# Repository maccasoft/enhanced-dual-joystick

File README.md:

## Enhanced Dual Joystick for RC2014

Add-on board designed for the [RC2014](http://rc2014.co.uk/) computer to provide an enhanced dual joystick port for games and other applications.

The board is based on a Z80 PIO that provide two 8-bit bi-direction parallel ports. Software can configure each port independently to use a standard Atari-compatibile joystick, a NES-compatible gamepad or any
other controller driven by digital I/O lines.

I/O ports can be configured with the on-board dip-switch.

### Schematics

| Parts List  |                                     |
| ----------- | ----------------------------------- |
| R1          | 10.000 ohm 1/4 watt                 |
| RN1, RN2    | 10.000 ohm, 9-pin resistor network  |
| RN3         | 10.000 ohm, 7-pin resistor network  |
| C1, C2      | 100.000 pF polyester                |
| IC1         | Z84C2010PEG                         |
| IC2         | CD74HCT688N                         |
| S1          | DIP-switch                          |
| CN1         | 40 pin male header, right angle     |
| CN2, CN3    | DB9 male connector                  |

Additionally, a NES-compatible gamepad board is included for those who don't have access to an existing joystick.

| Parts List            |                           |
| --------------------- | ------------------------- |
| R1-R8                 | 10.000 ohm 1/4 watt       |
| C1                    | 100.000 pF polyester      |
| IC1                   | CD4021                    |
| UP, DOWN, LEFT, RIGHT | 6x6 mm tact switches      |
| SELECT, START, B, A   | 6x6 mm tact switches      |
| CN1                   | 5-pin connector           |

### Code Examples

The Z80 PIO must be initialized at startup by configuring both ports in control mode 3 followed by the pin direction settings appropriate for
the game controller type.

**Atari 2600 joystick.**

```
PIO_BASE    .EQU    70H

            ; initialize

            LD      A,0CFH              ; set port A mode 3 (control)
            OUT     (PIO_BASE+1),A
            LD      A,0FFH              ; all pins as input
            OUT     (PIO_BASE+1),A

            LD      A,0CFH              ; set port B mode 3 (control)
            OUT     (PIO_BASE+3),A
            LD      A,0FFH              ; all pins as input
            OUT     (PIO_BASE+3),A

            ; read joystick 1

            IN      A,(PIO_BASE)

            ; read joystick 2

            IN      A,(PIO_BASE+2)
```

**NES gamepad on Joystick 2.**

The code assumes that the gamepad is wired to the DB9 connector as follows: 4=data, 5=load, 6=clk.  

```
PIO_BASE    .EQU    70H

NES_LOAD    .EQU    20H
NES_CLK     .EQU    10H

            ; initialize

            LD      A,0CFH              ; set port A mode 3 (control)
            OUT     (PIO_BASE+1),A
            LD      A,0FFH              ; all pins as input
            OUT     (PIO_BASE+1),A

            LD      A,0CFH              ; set port B mode 3 (control)
            OUT     (PIO_BASE+3),A
            LD      A,~(NES_LOAD|NES_CLK)   ; clock and load pins as output, others as input
            OUT     (PIO_BASE+3),A
            LD      A,0
            OUT     (PIO_BASE+2),A

            ; read joystick 1

            IN      A,(PIO_BASE)

            ; read joystick 2

            LD      C,0

            LD      A,NES_LOAD          ; pulse load pin
            OUT     ((PIO_BASE+2),A
            LD      A,0
            OUT     (PIO_BASE+2),A

            LD      B,8
L1:         IN      A,(PIO_BASE+2)      ; read data from bit 0
            RRA
            RL      C

            LD      A,NES_CLOCK         ; pulse clock
            OUT     (PIO_BASE+2),A
            LD      A,0
            OUT     (PIO_BASE+2),A

            DJNZ    L1

            LD      A,C
```

### Boards

Boards are shared on OSHPark:

[Dual Joystick](https://oshpark.com/shared_projects/1jlMB1r2)  
[Game Controller](https://oshpark.com/shared_projects/LxgxoR9j)  

A [donation](https://www.paypal.me/maccasoft/5eur) to support this and future projects is always welcome!

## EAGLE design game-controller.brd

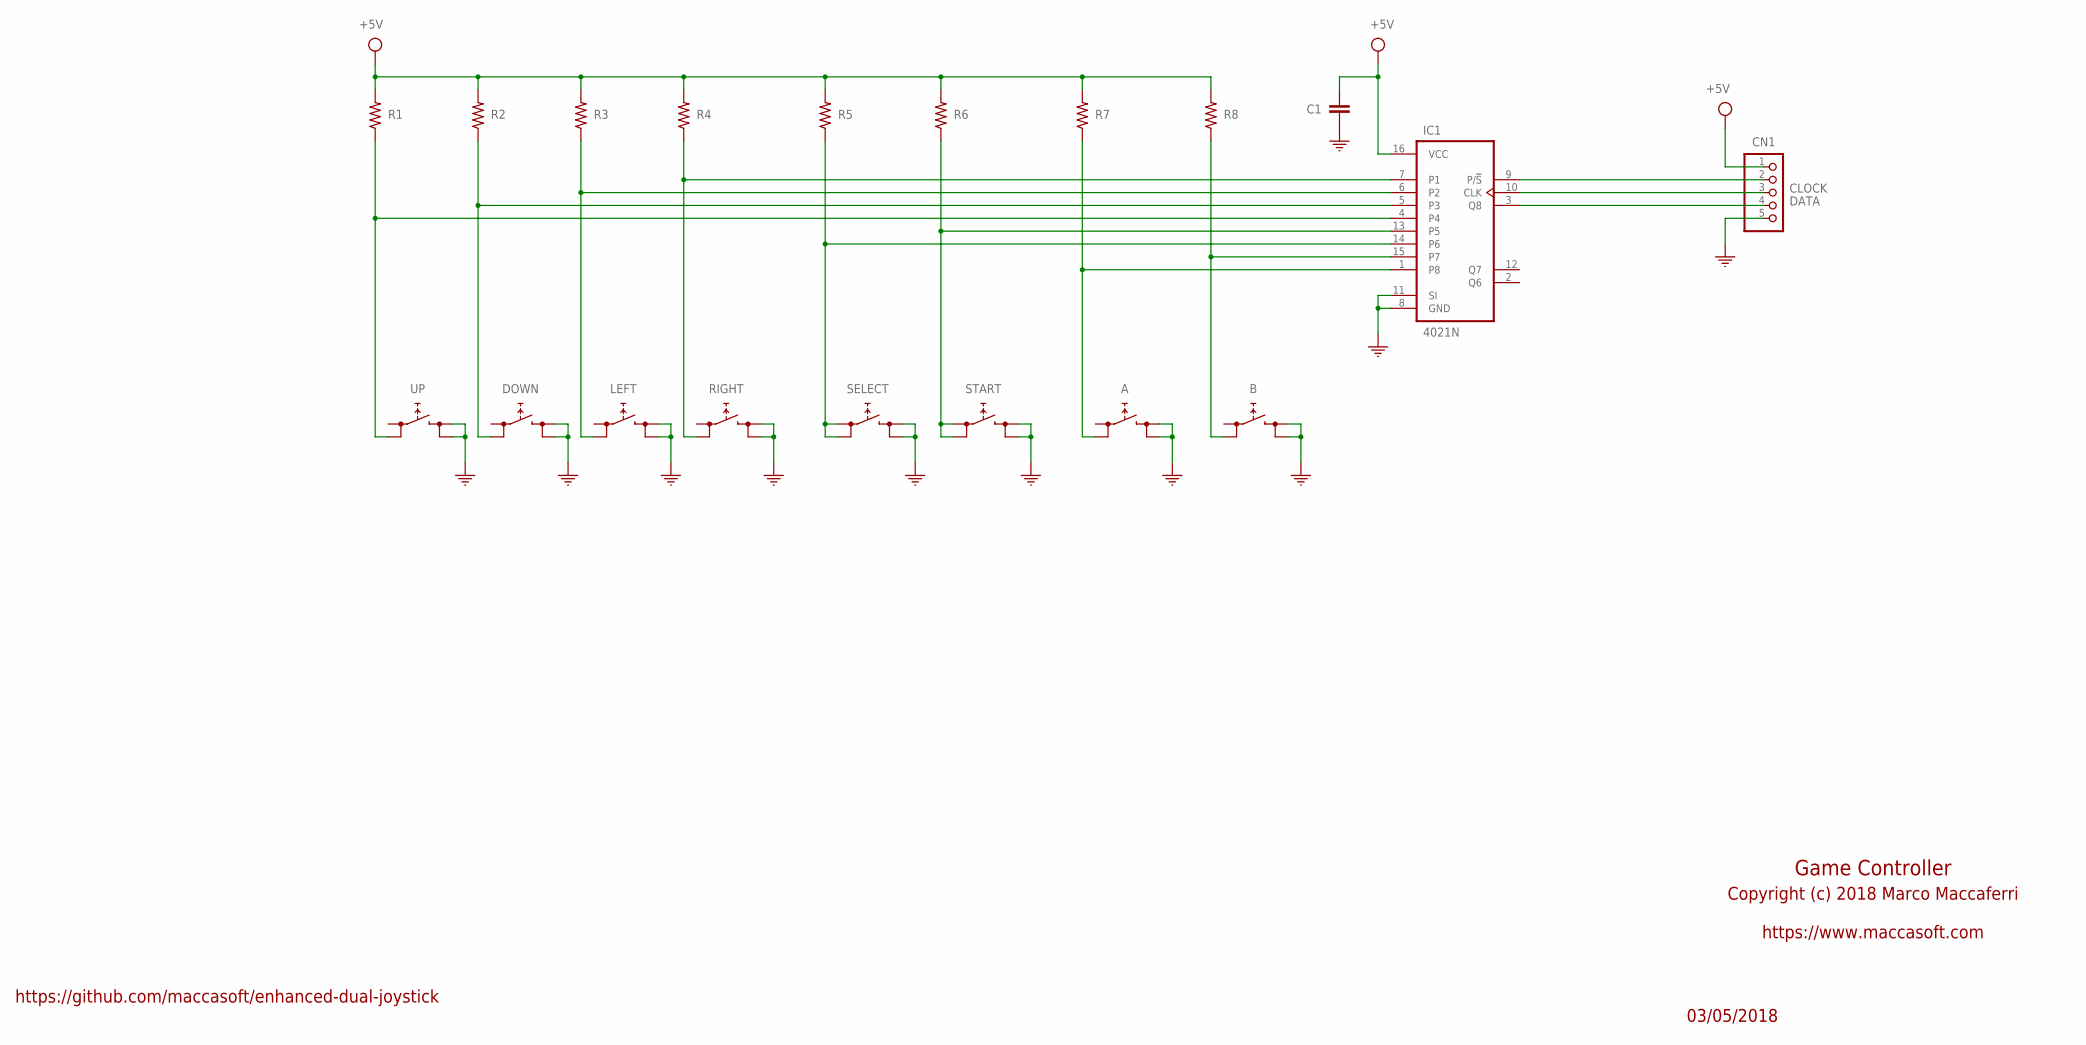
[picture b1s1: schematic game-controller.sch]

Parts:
A: FSM4JH; TL1105
B: FSM4JH; TL1105
C1: 100nF; C050-025X075; MPN R82EC3100AA70J
CN1: PINHD-1X5; 1X05
DOWN: FSM4JH; TL1105
IC1: 4021N; DIL16
LEFT: FSM4JH; TL1105
R1, R2, R3, R4, R5, R6, R7, R8: 10K; 0207/10; MPN CFR-25JB-52-10K
RIGHT: FSM4JH; TL1105
SELECT: FSM4JH; TL1105
START: FSM4JH; TL1105
UP: FSM4JH; TL1105

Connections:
+3.3V: C1.1, CN1.1, IC1.16 (VCC), R1.2, R2.2, R3.2, R4.2, R5.2, R6.2, R7.2, R8.2
A: A.3 (0), IC1.1 (P8), R7.1
B: B.3 (0), IC1.15 (P7), R8.1
CLOCK: CN1.3, IC1.10 (CLK)
DATA: CN1.4, IC1.3 (Q8)
DOWN: DOWN.3 (0), IC1.5 (P3), R2.1
GND: A.2 (1), A.4 (1), B.2 (1), B.4 (1), C1.2, CN1.5, DOWN.2 (1), DOWN.4 (1), IC1.8 (GND), IC1.11 (SI), LEFT.2 (1), LEFT.4 (1), RIGHT.2 (1), RIGHT.4 (1), SELECT.2 (1), SELECT.4 (1), START.2 (1), START.4 (1), UP.2 (1), UP.4 (1)
LEFT: IC1.6 (P2), LEFT.3 (0), R3.1
unnamed: CN1.2, IC1.9 (P/!S)
RIGHT: IC1.7 (P1), R4.1, RIGHT.3 (0)
SELECT: IC1.14 (P6), R5.1, SELECT.1 (0), SELECT.3 (0)
START: IC1.13 (P5), R6.1, START.1 (0), START.3 (0)
UP: IC1.4, R1.1, UP.3 (0)

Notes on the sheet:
Game Controller
03/05/2018
Copyright (c) 2018 Marco Maccaferri
https://github.com/maccasoft/enhanced-dual-joystick
https://www.maccasoft.com

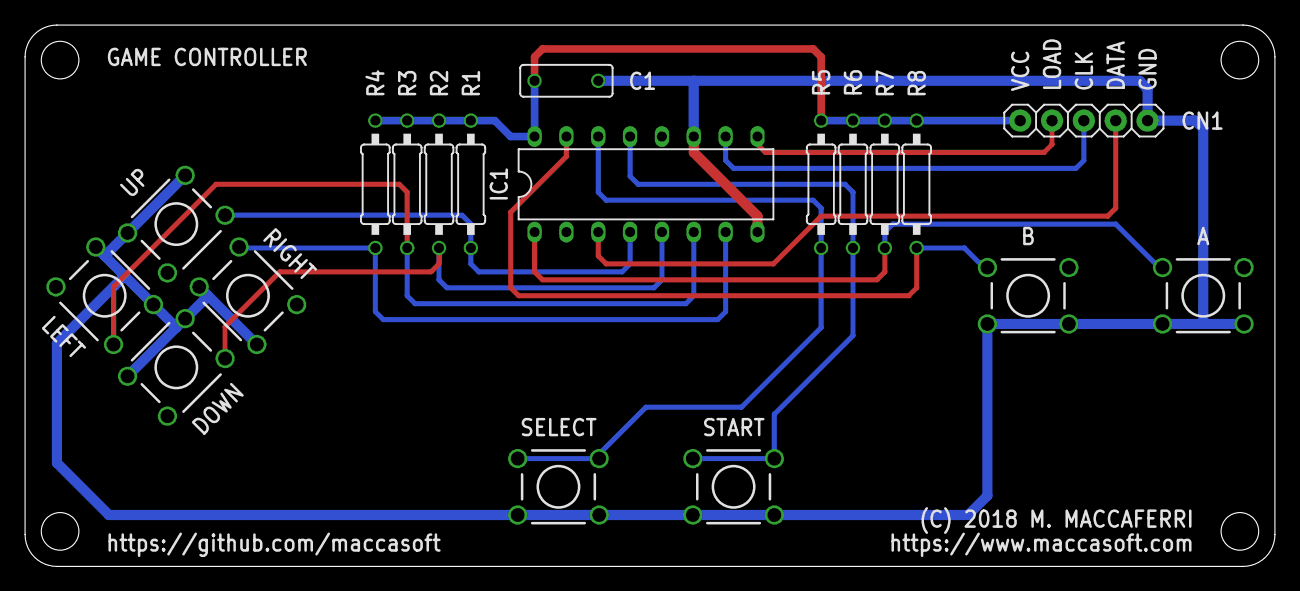
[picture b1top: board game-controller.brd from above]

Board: 2 copper layers, 99.7 x 43.2 mm, 19 parts (0 on the bottom side), 13 nets.

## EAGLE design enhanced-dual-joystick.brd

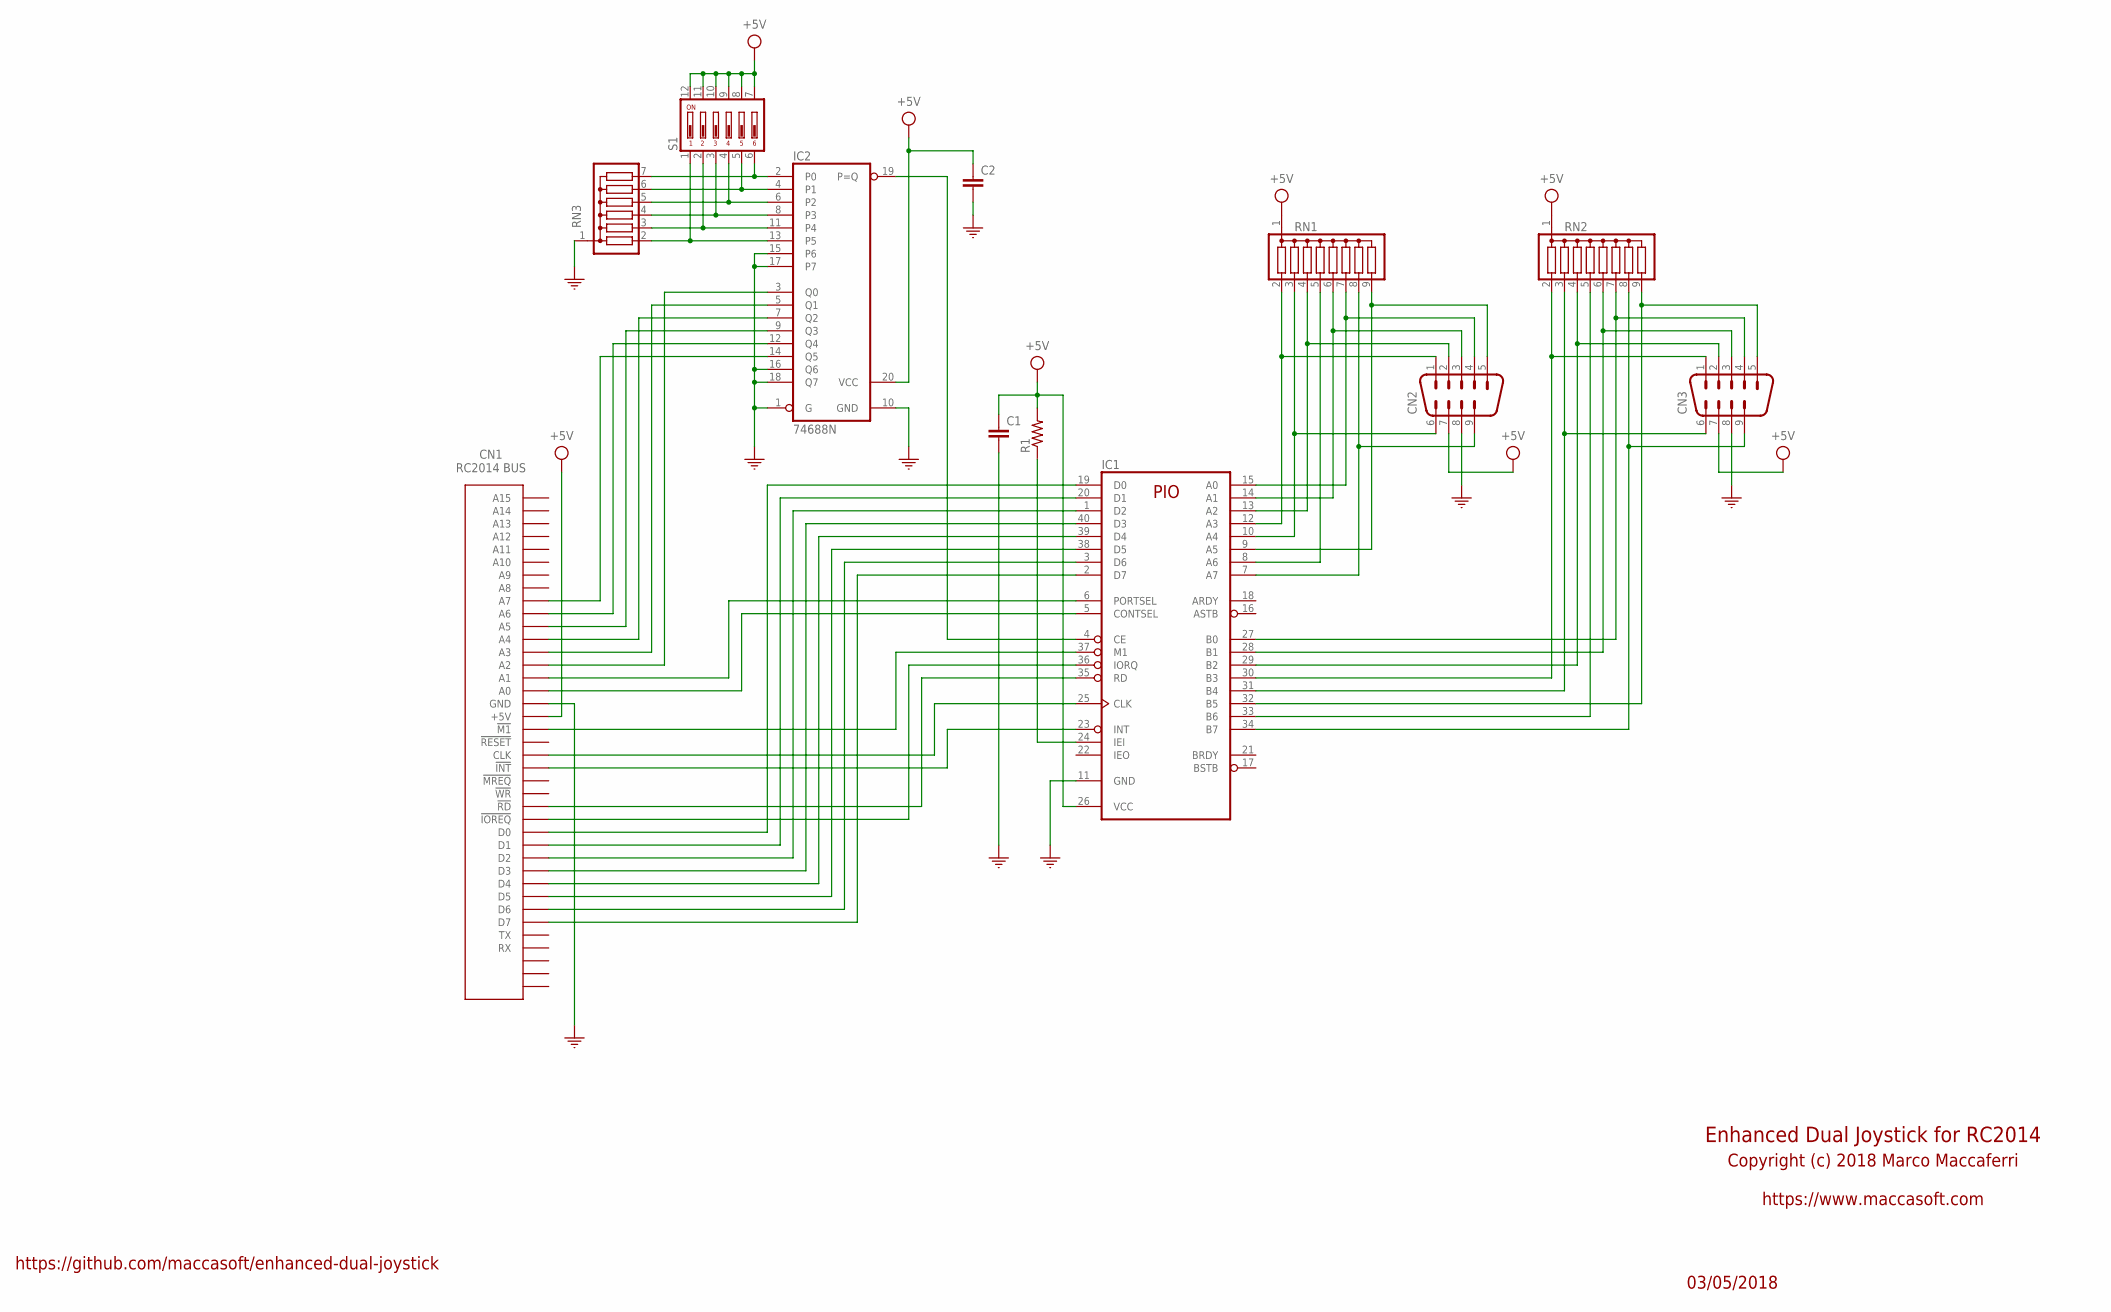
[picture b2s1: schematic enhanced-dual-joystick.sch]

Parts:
C1, C2: C-EU050-025X075; C050-025X075
CN1: RC2014BUS; MPN PRPC040SBAN-M71RC
CN2, CN3: M09H
IC1: Z80PIO; DIL40
IC2: 74688N; DIL20
R1: R-US_0207/10; 0207/10
RN1, RN2: G08R; SIL9
RN3: G06R; SIL7
S1: DIP06YL

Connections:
+5V: C1.1, C2.1, CN1.+5V, CN2.7, CN3.7, IC1.26 (VCC), IC2.20 (VCC), R1.2, RN1.1, RN2.1, S1.7, S1.8, S1.9, S1.10, S1.11, S1.12
GND: C1.2, C2.2, CN1.GND, CN2.8, CN3.8, IC1.11 (GND), IC2.1 (G), IC2.10 (GND), IC2.15 (P6), IC2.16 (Q6), IC2.17 (P7), IC2.18 (Q7), RN3.1
unnamed: CN2.1, IC1.12 (A3), RN1.2
unnamed: CN2.6, IC1.10 (A4), RN1.3
unnamed: CN2.2, IC1.13 (A2), RN1.4
unnamed: IC1.8 (A6), RN1.5
unnamed: CN2.3, IC1.14 (A1), RN1.6
unnamed: CN2.4, IC1.15 (A0), RN1.7
unnamed: CN2.9, IC1.7 (A7), RN1.8
unnamed: CN2.5, IC1.9 (A5), RN1.9
unnamed: IC2.2 (P0), RN3.7, S1.6
unnamed: IC2.4 (P1), RN3.6, S1.5
unnamed: IC2.6 (P2), RN3.5, S1.4
unnamed: IC2.8 (P3), RN3.4, S1.3
unnamed: IC2.11 (P4), RN3.3, S1.2
unnamed: IC2.13 (P5), RN3.2, S1.1
unnamed: CN1.A7, IC2.14 (Q5)
unnamed: CN1.A6, IC2.12 (Q4)
unnamed: CN1.D7, IC1.2 (D7)
unnamed: CN1.D6, IC1.3 (D6)
unnamed: CN1.D5, IC1.38 (D5)
unnamed: CN1.D4, IC1.39 (D4)
unnamed: CN1.D3, IC1.40 (D3)
unnamed: CN1.D2, IC1.1 (D2)
unnamed: CN1.D1, IC1.20 (D1)
unnamed: CN1.D0, IC1.19 (D0)
unnamed: CN1.!IOREQ!, IC1.36 (IORQ)
unnamed: CN1.!RD!, IC1.35 (RD)
unnamed: CN1.!M1!, IC1.37 (M1)
unnamed: CN1.CLK, IC1.25 (CLK)
unnamed: CN1.!INT!, IC1.23 (INT)
unnamed: CN1.A5, IC2.9 (Q3)
unnamed: CN1.A4, IC2.7 (Q2)
unnamed: CN1.A3, IC2.5 (Q1)
unnamed: CN1.A2, IC2.3 (Q0)
unnamed: IC1.4 (CE), IC2.19 (P=Q)
unnamed: CN1.A1, IC1.6 (PORTSEL)
unnamed: CN1.A0, IC1.5 (CONTSEL)
unnamed: IC1.33 (B6), RN2.5
unnamed: IC1.24 (IEI), R1.1
unnamed: CN3.1, IC1.30 (B3), RN2.2
unnamed: CN3.6, IC1.31 (B4), RN2.3
unnamed: CN3.2, IC1.29 (B2), RN2.4
unnamed: CN3.3, IC1.28 (B1), RN2.6
unnamed: CN3.4, IC1.27 (B0), RN2.7
unnamed: CN3.9, IC1.34 (B7), RN2.8
unnamed: CN3.5, IC1.32 (B5), RN2.9

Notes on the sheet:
CN1 RC2014 BUS
Enhanced Dual Joystick for RC2014
03/05/2018
Copyright (c) 2018 Marco Maccaferri
https://github.com/maccasoft/enhanced-dual-joystick
https://www.maccasoft.com

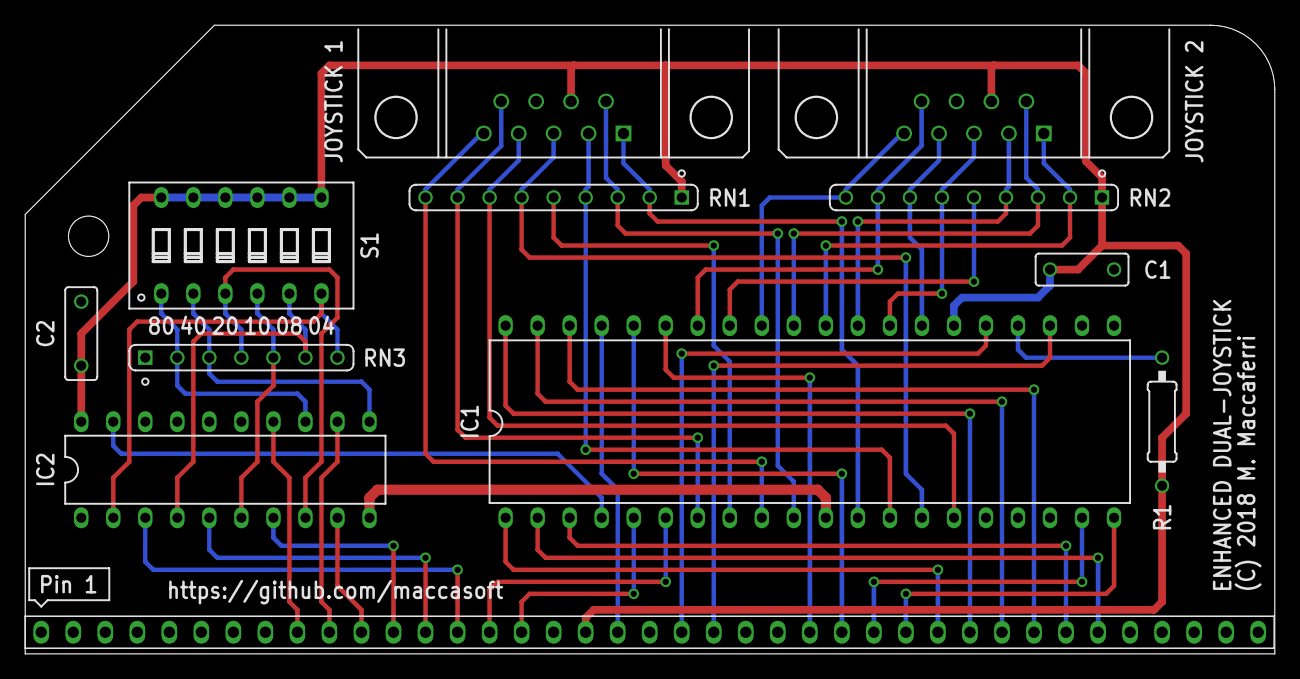
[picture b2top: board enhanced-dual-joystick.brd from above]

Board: 2 copper layers, 99.1 x 49.9 mm, 12 parts (0 on the bottom side), 47 nets.

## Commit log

2018-05-03 Repository setup
2018-05-04 Added board schematics, pcb and gerber files
2018-05-05 Added README

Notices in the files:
enhanced-dual-joystick.brd:
(C) 2018 M. Maccaferri
